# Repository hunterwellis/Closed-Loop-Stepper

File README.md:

# Closed-Loop-Stepper

A stepper motor using daisey-chained CAN and power connections. Fits on the back of NEMA17 4-wire bipolar stepper motor.

The end goal of this project is to implement a FOC agorithm to control the stepper in closed loop.

*Image of first power test*

## Usage
Install ST and ARM-GNU toolchains.
```
sudo apt install stlink-tools gcc-arm-none-eabi
```
This the firmware for this board is written using libopencm3 (an open-sourced hardware library for ARM Cortex-M3 microcontrollers). Make sure to clone and build libopencm3 in the project repo.
```
git submodule update --init --recursive
```
This design is programmed via SWD (using an ST-Link) -- to build and flash the firmware.
```
cd ./2.Firmware/Base_Driver/src
make
st-flash --reset write base-driver.bin 0x800000
```

*KiCAD render of PCBA*

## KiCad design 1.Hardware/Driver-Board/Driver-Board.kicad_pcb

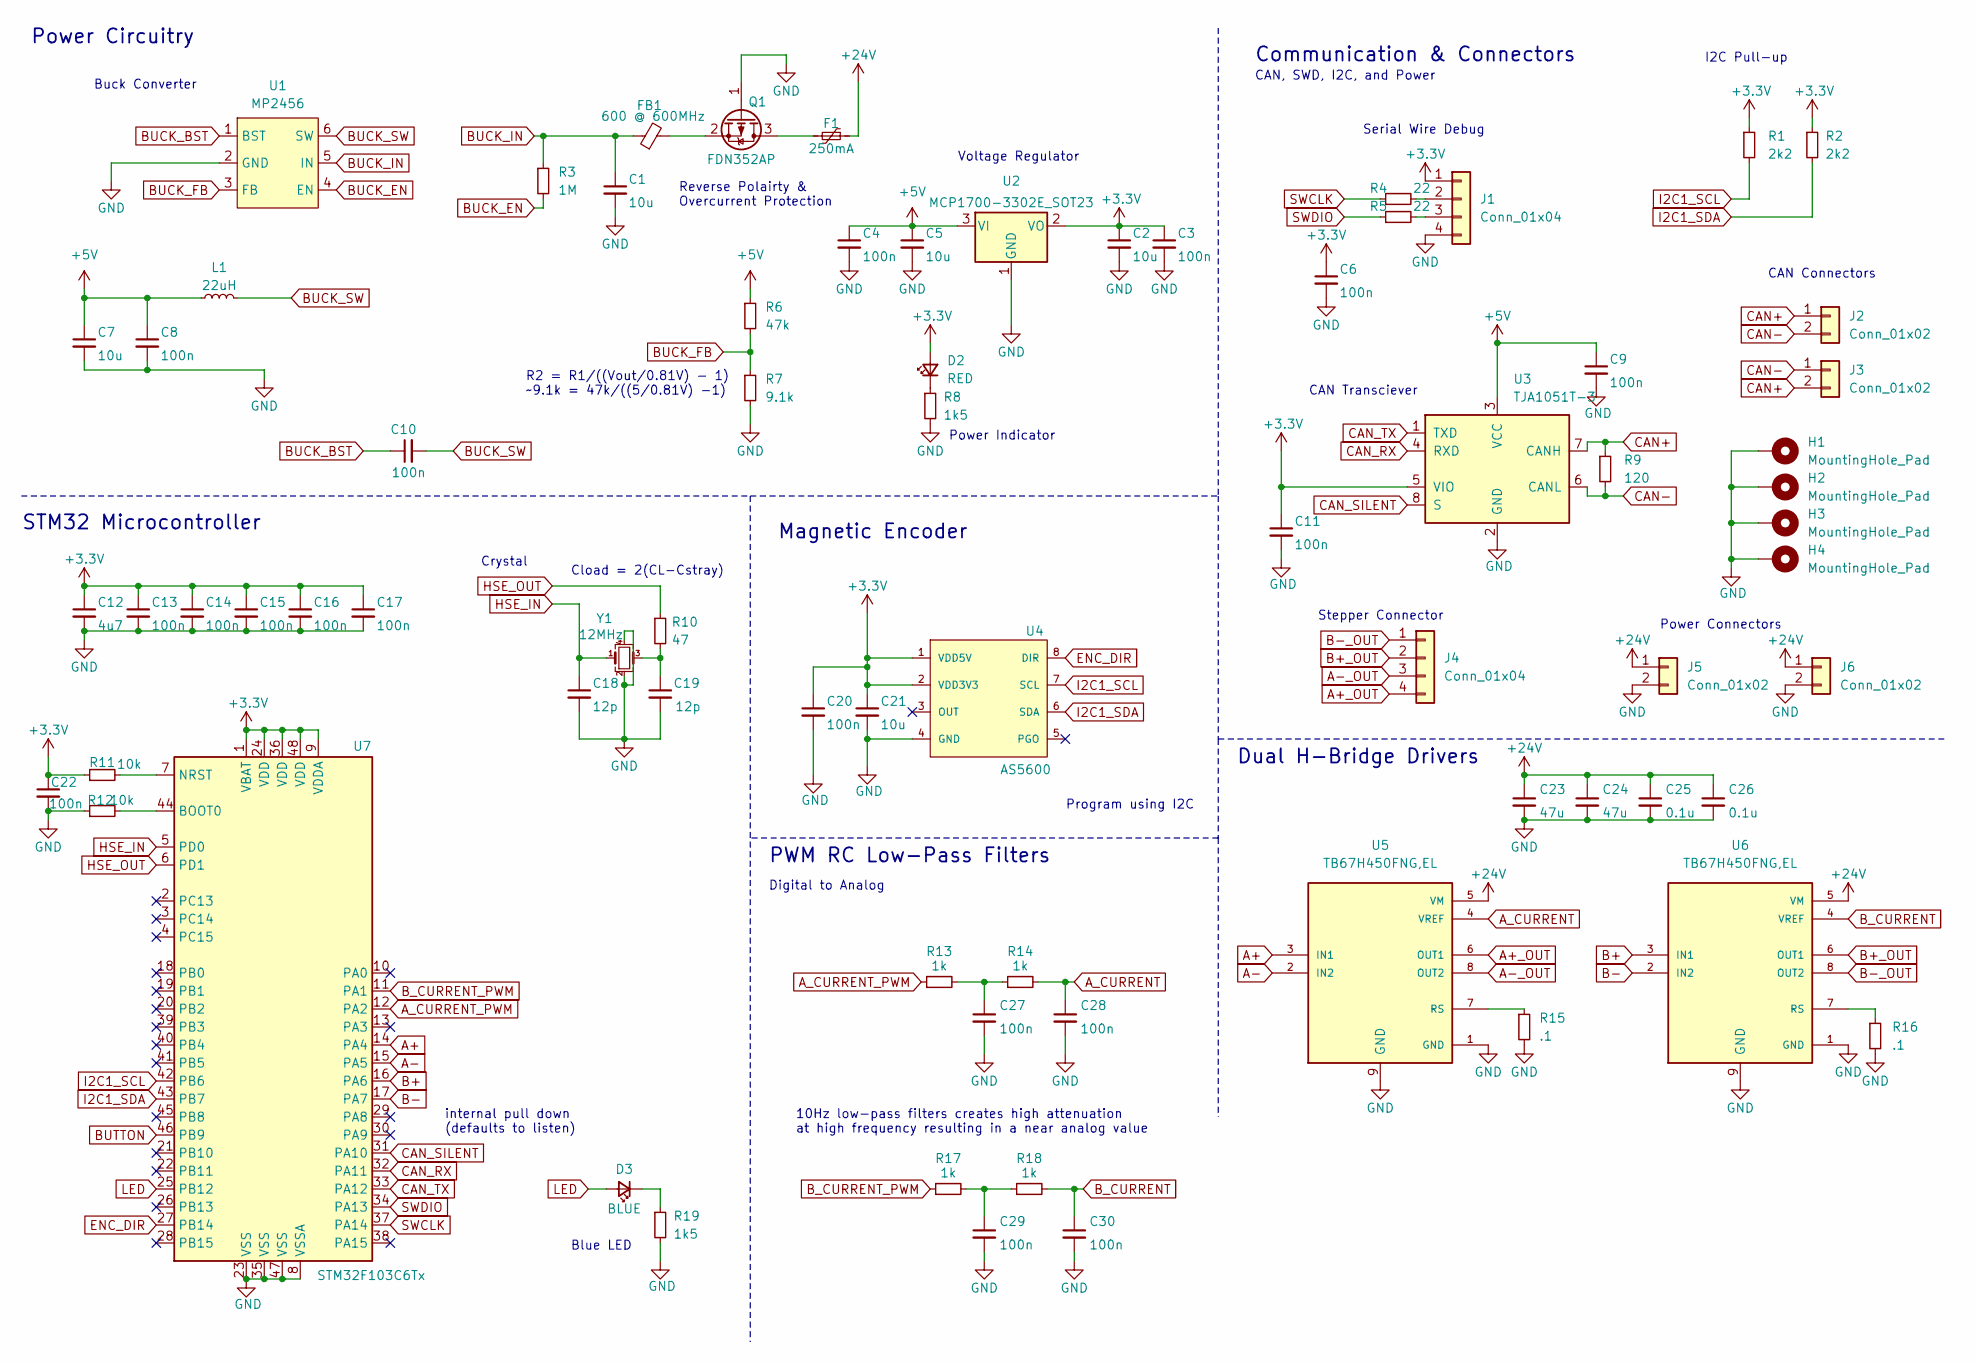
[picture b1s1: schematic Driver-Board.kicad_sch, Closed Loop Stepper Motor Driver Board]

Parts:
C1: 10u; C_1206_3216Metric
C2, C5, C7: 10u; C_0603_1608Metric
C3, C4, C8, C10: 100n; C_0603_1608Metric
C6, C9, C11, C13, C14, C15, C16, C17, C20, C22, C27, C28, C29, C30: 100n; C_0402_1005Metric
C12: 4u7; C_0603_1608Metric
C18, C19: 12p; C_0402_1005Metric
C21: 10u; C_0402_1005Metric
C23, C24: 47u; C_1206_3216Metric
C25, C26: 0.1u; C_1206_3216Metric
D2: RED; LED_0603_1608Metric
D3: BLUE; LED_0603_1608Metric
F1: 250mA; Fuse_1206_3216Metric
FB1: 600 @ 600MHz; L_0805_2012Metric
H1, H2, H3, H4: MountingHole_Pad; MountingHole_3.2mm_M3_Pad_Via
J1: Conn_01x04; PinHeader_1x04_P2.54mm_Vertical
J2, J3: Conn_01x02; Molex_PicoBlade_53048-0210_1x02_P1.25mm_Horizontal
J4: Conn_01x04; Stepper Wire Connector
J5, J6: Conn_01x02; 24V Split Power Connection
L1: 22uH; L_Sunlord_MWSA0518_5.4x5.2mm
Q1: FDN352AP; SuperSOT-3
R1, R2: 2k2; R_0603_1608Metric
R3: 1M; R_1206_3216Metric
R4, R5: 22; R_0402_1005Metric
R6: 47k; R_0603_1608Metric
R7: 9.1k; R_0603_1608Metric
R8, R19: 1k5; R_0603_1608Metric
R9: 120; R_0603_1608Metric
R10: 47; R_0402_1005Metric
R11, R12: 10k; R_0402_1005Metric
R13, R14, R17, R18: 1k; R_0402_1005Metric
R15, R16: .1; R_1206_3216Metric
U1: MP2456; TSOT-23-6
U2: MCP1700-3302E_SOT23; SOT-23
U3: TJA1051T-3; SOIC-8_3.9x4.9mm_P1.27mm
U4: AS5600; SOIC-8_3.9x4.9mm_P1.27mm
U5, U6: TB67H450FNG,EL; SOIC127P599X175-9N; PARTREV 3.0
U7: STM32F103C6Tx; LQFP-48_7x7mm_P0.5mm
Y1: 12MHz; Crystal_SMD_3225-4Pin_3.2x2.5mm

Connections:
+3.3V: C2.1, C3.1, C6.1, C11.1, C12.1, C13.1, C14.1, C15.1, C16.1, C17.1, C20.1, C21.1, C22.1, D2.2 (A), J1.1, R1.1, R2.1, R11.1, U2.2 (VO), U3.5 (VIO), U4.1 (VDD5V), U4.2 (VDD3V3), U7.1 (VBAT), U7.9 (VDDA), U7.24 (VDD), U7.36 (VDD), U7.48 (VDD)
+5V: C4.1, C5.1, C7.1, C8.1, C9.1, L1.1, R6.1, U2.3 (VI), U3.3 (VCC)
+24V: C23.1, C24.1, C25.1, C26.1, F1.1, J5.1, J6.1, U5.5 (VM), U6.5 (VM)
A+: U5.3 (IN1), U7.14 (PA4)
A+_OUT: J4.4, U5.6 (OUT1)
A-: U5.2 (IN2), U7.15 (PA5)
A-_OUT: J4.3, U5.8 (OUT2)
A_CURRENT: C28.1, R14.2, U5.4 (VREF)
A_CURRENT_PWM: R13.1, U7.12 (PA2)
B+: U6.3 (IN1), U7.16 (PA6)
B+_OUT: J4.2, U6.6 (OUT1)
B-: U6.2 (IN2), U7.17 (PA7)
B-_OUT: J4.1, U6.8 (OUT2)
BUCK_BST: C10.1, U1.1 (BST)
BUCK_EN: R3.2, U1.4 (EN)
BUCK_FB: R6.2, R7.1, U1.3 (FB)
BUCK_IN: C1.1, FB1.1, R3.1, U1.5 (IN)
BUCK_SW: C10.2, L1.2, U1.6 (SW)
BUTTON: U7.46 (PB9); also elsewhere on the board
B_CURRENT: C30.1, R18.2, U6.4 (VREF)
B_CURRENT_PWM: R17.1, U7.11 (PA1)
CAN+: J2.1, J3.2, R9.1, U3.7 (CANH)
CAN-: J2.2, J3.1, R9.2, U3.6 (CANL)
CAN_RX: U3.4 (RXD), U7.32 (PA11)
CAN_SILENT: U3.8 (S), U7.31 (PA10)
CAN_TX: U3.1 (TXD), U7.33 (PA12)
ENC_DIR: U4.8 (DIR), U7.27 (PB14)
GND: C1.2, C2.2, C3.2, C4.2, C5.2, C6.2, C7.2, C8.2, C9.2, C11.2, C12.2, C13.2, C14.2, C15.2, C16.2, C17.2, C18.2, C19.2, C20.2, C21.2, C22.2, C23.2, C24.2, C25.2, C26.2, C27.2, C28.2, C29.2, C30.2, H1.1, H2.1, H3.1, H4.1, J1.4, J5.2, J6.2, Q1.1 (G), R7.2, R8.2, R12.1, R15.2, R16.2, R19.2, U1.2 (GND), U2.1 (GND), U3.2 (GND), U4.4 (GND), U5.1 (GND), U5.9 (GND), U6.1 (GND), U6.9 (GND), U7.8 (VSSA), U7.23 (VSS), U7.35 (VSS), U7.47 (VSS), Y1.2, Y1.4; also elsewhere on the board
HSE_IN: C18.1, U7.5 (PD0), Y1.1
HSE_OUT: R10.1, U7.6 (PD1)
I2C1_SCL: R1.2, U4.7 (SCL), U7.42 (PB6)
I2C1_SDA: R2.2, U4.6 (SDA), U7.43 (PB7)
LED: D3.2 (A), U7.25 (PB12)
unnamed: C19.1, R10.2, Y1.3
unnamed: C27.1, R13.2, R14.1
unnamed: C29.1, R17.2, R18.1
unnamed: D2.1 (K), R8.1
unnamed: D3.1 (K), R19.1
unnamed: J1.2, R4.2
unnamed: J1.3, R5.2
unnamed: F1.2, Q1.3 (D)
unnamed: FB1.2, Q1.2 (S)
unnamed: R15.1, U5.7 (RS)
unnamed: R16.1, U6.7 (RS)
unnamed: R12.2, U7.44 (BOOT0)
unnamed: R11.2, U7.7 (NRST)
SWCLK: R4.1, U7.37 (PA14)
SWDIO: R5.1, U7.34 (PA13)

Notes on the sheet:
CAN, SWD, I2C, and Power
Reverse Polairty & Overcurrent Protection
CAN Transciever
Cload = 2(CL-Cstray)
Buck Converter
Voltage Regulator
Power Connectors
Dual H-Bridge Drivers
Blue LED
Crystal
Power Circuitry
Power Indicator
internal pull down (defaults to listen)
Magnetic Encoder
R2 = R1/((Vout/0.81V) - 1) ~9.1k = 47k/((5/0.81V) -1)
STM32 Microcontroller
CAN Connectors
Communication & Connectors
PWM RC Low-Pass Filters
Serial Wire Debug
Program using I2C
10Hz low-pass filters creates high attenuation at high frequency resulting in a near analog value
I2C Pull-up
Digital to Analog
Stepper Connector

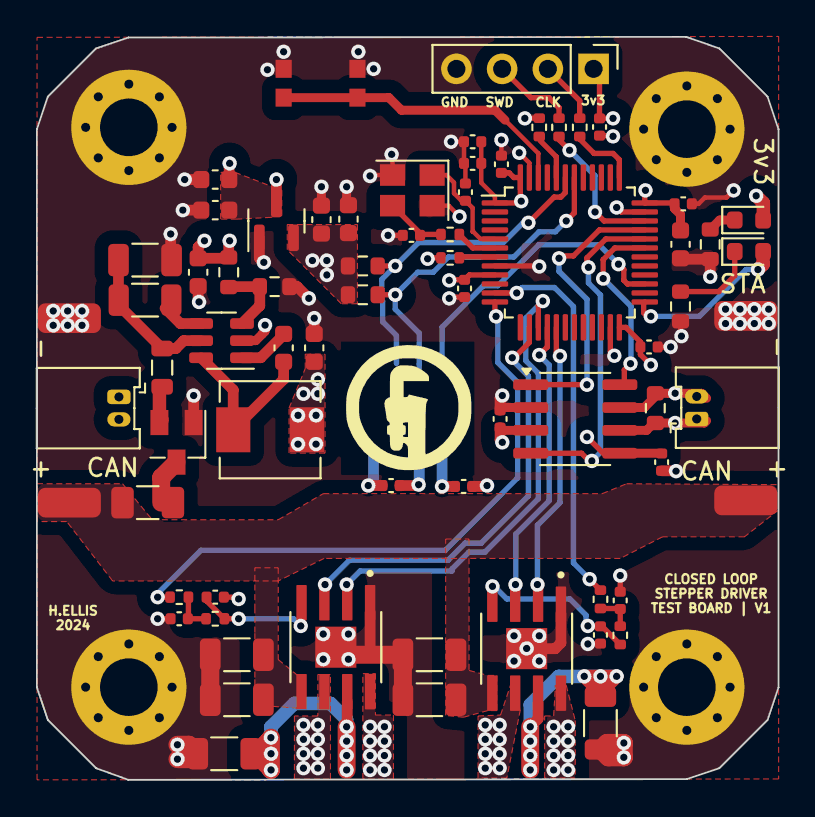
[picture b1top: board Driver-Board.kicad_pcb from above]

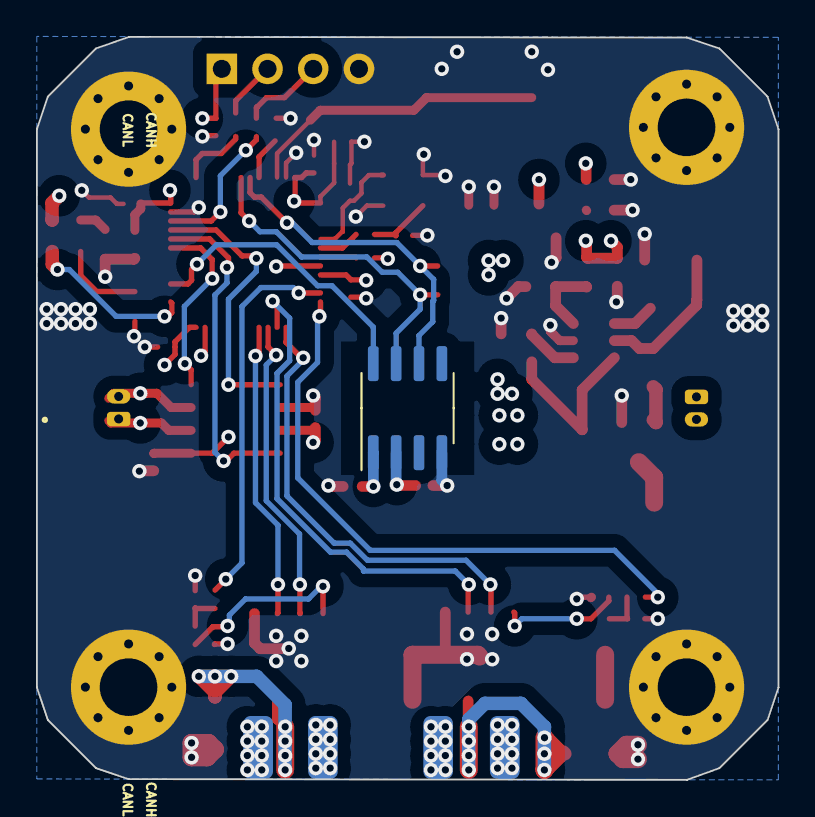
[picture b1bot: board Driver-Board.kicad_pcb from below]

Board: 4 copper layers, 41.2 x 41.3 mm, 74 parts (2 on the bottom side), 48 nets.

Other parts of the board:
SW1: SW_Push; KMR731NG LFS

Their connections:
BUTTON: SW1.2; also elsewhere on the board
GND: SW1.1; also elsewhere on the board

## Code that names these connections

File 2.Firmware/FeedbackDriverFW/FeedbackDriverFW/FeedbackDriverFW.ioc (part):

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Mcu.Name=STM32F103C(4-6)Tx
Mcu.Package=LQFP48
Mcu.UserName=STM32F103C6Tx
PA1.GPIOParameters=GPIO_Label
PA1.GPIO_Label=B_CURRENT_PWM
PA1.Signal=S_TIM2_CH2
PA10.GPIOParameters=GPIO_PuPd,GPIO_Label
PA10.GPIO_Label=CAN_SILENT
PA10.GPIO_PuPd=GPIO_PULLDOWN
PA10.Signal=GPIO_Output
PA11.Mode=CAN_Activate
PA11.Signal=CAN_RX
PA12.Mode=CAN_Activate
PA12.Signal=CAN_TX
PA13.Mode=Trace_Asynchronous_SW
PA13.Signal=SYS_JTMS-SWDIO
PA14.Mode=Trace_Asynchronous_SW
PA14.Signal=SYS_JTCK-SWCLK
PA2.GPIOParameters=GPIO_Label
PA2.GPIO_Label=A_CURRENT_PWM
PA2.Signal=S_TIM2_CH3
PA4.GPIOParameters=GPIO_Label
PA4.GPIO_Label=B_MINUS
PA4.Signal=GPIO_Output
PA5.GPIOParameters=GPIO_Label
PA5.GPIO_Label=B_PLUS
PA5.Signal=GPIO_Output
PA6.GPIOParameters=GPIO_Label
PA6.GPIO_Label=A_MINUS
PA6.Signal=GPIO_Output
PA7.GPIOParameters=GPIO_Label
PA7.GPIO_Label=A_PLUS
PA7.Signal=GPIO_Output
PB12.GPIOParameters=GPIO_Label
PB12.GPIO_Label=LED
PB12.Signal=GPIO_Output
PB14.GPIOParameters=GPIO_Label
PB14.GPIO_Label=ENC_DIR
PB14.Signal=GPIO_Output
PB3.Mode=Trace_Asynchronous_SW
PB3.Signal=SYS_JTDO-TRACESWO
PB6.Mode=I2C
PB6.Signal=I2C1_SCL
PB7.Mode=I2C
PB7.Signal=I2C1_SDA
PB9.GPIOParameters=GPIO_Label
PB9.GPIO_Label=B1
PB9.Signal=GPXTI9
PD0-OSC_IN.Mode=HSE-External-Oscillator
PD0-OSC_IN.Signal=RCC_OSC_IN
PD1-OSC_OUT.Mode=HSE-External-Oscillator
PD1-OSC_OUT.Signal=RCC_OSC_OUT
RCC.HSEDivPLL=RCC_HSE_PREDIV_DIV2
RCC.HSE_VALUE=16000000
RCC.SYSCLKFreq_VALUE=72000000
RCC.SYSCLKSource=RCC_SYSCLKSOURCE_PLLCLK
board=custom

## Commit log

2024-06-09 init commit
2024-10-27 updated board
2024-11-08 corrected power trace
2024-11-11 .ioc config
2024-11-11 added basic driver
2024-11-12 as5600 integration
2024-11-18 updated BOM
2024-11-18 init libopencm3 commit
2024-11-18 init i2c
2025-03-11 libopencm3 integration and power test
